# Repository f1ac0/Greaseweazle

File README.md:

# Greaseweazle
The Greaseweazle project by Keir Fraser is a USB floppy drive interface and software tool to read and write disk images to and from real floppies. It works at a low level so it can deal with formats that are unknown to the standard PC floppy disk controller.
https://github.com/keirf/Greaseweazle

The project in this repository is just a recreated "F1" board making use of the bare chips instead of a bluepill module, and designed to plug directly into a standard PC drive.
- It is small : it fits inside the 3.5" drive height and the ribbon width
- It is equipped with the female 34 pin connector to conveniently plug it in the drive, without a ribbon cable
- It connects to the PC with a micro USB cable
- It has a pass-through header for powering the drive (5v only). An external 5v/12v PSU is required only for drives requiring 12v or power hungry ones.
- It uses SMD stuff (maybe harder to solder)
- It is designed using the KiCAD EDA
- It works with the original "F1" Greaseweazle firmware and tool
- It is updated to support the DISKCHANGE signal and to be able to report as a "F1 plus" board. This is necessary for the WinUAE FloppyBridge plugin by Robert Smith (http://amiga.robsmithdev.co.uk/winuae) who added support to the Greaseweazle in addition to his original DrawBridge interface. Thank you !
- It does not have the "F7" features like double drive support

# Disclaimer
This is a hobbyist project, it comes with no warranty and no support.

This version is not endorsed by the original author, please don't bother him with issues you might have because of it.

I publish this work using the same license as the original : The Unlicense.

If you find it useful, please reward the original author.

# BOM
- 1x STM32F103C8T6 or CS32F103C8T6
- 1x 3.3v LDO, either SPX3819M5-L-3-3 or XC6206P332MR or equivalent
- 1x 8MHz HC-49 crystal
- 2x 1uF 0805 capacitors
- 3x 100nF 0805 capacitors
- 2x 22pf 0805 capacitors
- 2x 22 ohm 0805 resistors
- 1x 1K 0805 resistor
- 1x 10K 0805 resistor
- 1x 100K 0805 resistor (to reduce the BOM you can use a 10k)
- 1x 1K 0603x4 resistor array
- 1x optional 0805 LED and 0805 resistor (330 ohm or more)
- 1x Micro USB Female Socket B type
- 1x 2x17 2.54mm pin socket
- 1x FDD power cable

# Making it
Check for shorts at least between 5V, 3.3V, and GND traces before applying power !

The programming port does not need to be soldered since it needs to be programmed just once : you can just hold it in place during the few seconds required for programming.

For the software part, it works with the original "F1" firmware and tool.

There are ID pads on the bottom of the board :
- with ID pads left open, it will be identified as a "F1" version.
- recommended for FloppyBridge plugin : use a recent firmware and close ID0 on the "2" side, make sure the "1" side is open, then it will be identified as a "F1 plus".

To program the uC, I personally use a STLINK clone dongle with the stlink tool : https://github.com/stlink-org/stlink
```
st-flash --format ihex write Greaseweazle-F1-v0.??.hex
```
To update through the USB cable, bridge CK and GND on the programming port before connecting the USB cable, then enter
```
Greaseweazle/gw update
```

# Using it
Choose a PC drive. Do not use a Shugart drive from your Amiga. Prefer a 5v one that does not require a 12V rail.
- Plug the board to the 34 pin connector of the PC drive,
- If your drive is 5v only, plug the power cord from the Greaseweazle board to the power plug of the drive,
- If the drive needs 12v, or if your USB source does not deliver enough current, then use an external power supply instead,
- Plug a micro USB cable to the device,
- Then install it and use it like an original Greaseweazle device : https://github.com/keirf/Greaseweazle/wiki/Software-Installation
```
Greaseweazle/gw read mydisk.scp
Greaseweazle/gw write mydisk.scp
```

To use it with WinUAE, see : http://amiga.robsmithdev.co.uk/winuae

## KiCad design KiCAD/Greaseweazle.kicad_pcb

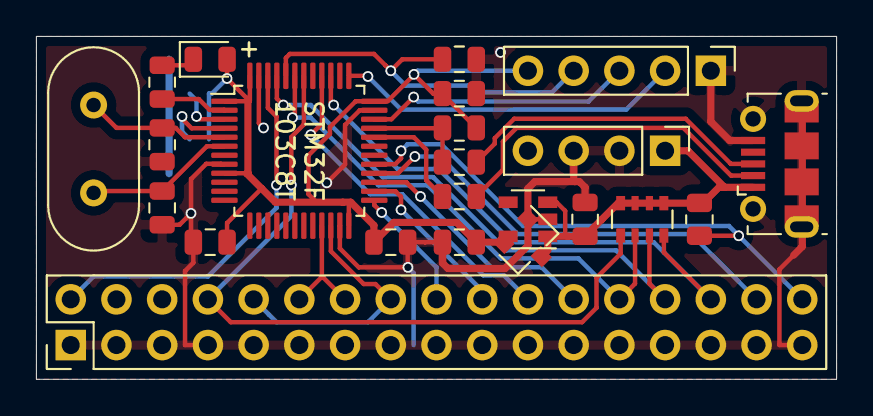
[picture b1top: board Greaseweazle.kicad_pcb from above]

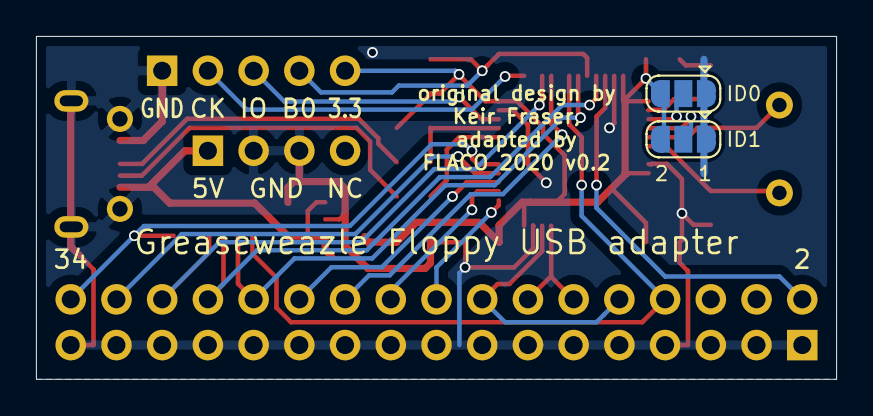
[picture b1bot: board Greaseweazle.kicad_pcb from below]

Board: 2 copper layers, 44.5 x 19.0 mm, 25 parts (2 on the bottom side), 29 nets.

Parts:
C1, C2: 22p; C_0805_2012Metric
C4, C5: 1u; C_0805_2012Metric
C6, C7, C8: 100n; C_0805_2012Metric
D1: Blue; LED_0805_2012Metric
J1: USB_B_Micro; USB_Micro-B_Molex-105017-0001
J2: PROG; PinHeader_1x05_P2.54mm_Vertical
J3: POWER; PinHeader_1x04_P2.54mm_Vertical
J4: Conn_02x17_Odd_Even; PinHeader_2x17_P2.54mm_Vertical
JP1: ID0; SolderJumper-3_P1.3mm_Open_RoundedPad1.0x1.5mm
JP2: ID1; SolderJumper-3_P1.3mm_Open_RoundedPad1.0x1.5mm
R2: 510; R_0805_2012Metric
R3: 100k; R_0805_2012Metric
R4: 1k; R_0805_2012Metric
R5: 10k; R_0805_2012Metric
R6, R7: 22; R_0805_2012Metric
RN1: 1k; R_Array_Convex_4x0603
U1: SPX3819M5-L-3-3; SOT-23-5
U2: STM32F103C8Tx; LQFP-48_7x7mm_P0.5mm
U3: XC6206PxxxMR; SOT-23
Y1: 8M; Crystal_HC49-U_Vertical

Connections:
+3V3: C5.1, C6.1, C7.1, C8.1, D1.2, J2.5, JP1.3, JP2.3, R5.1, U1.5, U2.1, U2.9, U2.24, U2.36, U2.48, U3.2
+5V: C4.1, J1.1, J3.1, R4.1, RN1.5, RN1.6, RN1.7, RN1.8, U1.1, U1.3, U3.3
/BOOT0: J2.4, R3.1, U2.44
/ID0: JP1.2, U2.3
/ID1: JP2.2, U2.4
/LED: R2.2, U2.2
/SWCLK: J2.2, U2.37
/SWDIO: J2.3, U2.34
/USB_D+: J1.3, R7.1
/USB_D-: J1.2, R6.1
/_DENSEL: J4.2, U2.46
/_DIR: J4.18, U2.25
/_DKRD: J4.30, RN1.4, U2.39
/_DKWD: J4.22, U2.40
/_DKWE: J4.24, U2.27
/_DSKCHG: J4.34, R4.2, U2.29
/_INDEX: J4.8, RN1.1, U2.42
/_MTR: J4.10, J4.16, U2.22
/_SEL: J4.12, J4.14, U2.21
/_SIDE: J4.32, U2.28
/_STEP: J4.20, U2.26
/_TRK0: J4.26, RN1.2, U2.43
/_WRPROT: J4.28, RN1.3, U2.45
GND: C1.2, C2.2, C4.2, C5.2, C6.2, C7.2, C8.2, J1.5, J1.6, J2.1, J3.2, J3.3, J4.1, J4.3, J4.5, J4.7, J4.9, J4.11, J4.13, J4.15, J4.17, J4.19, J4.21, J4.23, J4.25, J4.27, J4.29, J4.31, J4.33, JP1.1, JP2.1, R3.2, U1.2, U2.8, U2.23, U2.35, U2.47, U3.1
unnamed: C1.1, U2.5, Y1.1
unnamed: C2.1, U2.6, Y1.2
unnamed: D1.1, R2.1
unnamed: R5.2, R7.2, U2.33
unnamed: R6.2, U2.32

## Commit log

2020-07-31 Respository init with v0.1 KiCAD files, Readme and License
2021-06-08 Kicad : 0.2 with additional regulator footprint, DISKCHANGE signal and ID jumpers
2022-02-16 Photo, InteractiveHtmlBom and README

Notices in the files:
KiCAD/Greaseweazle.kicad_pcb:
FLACO 2019, original schematic by Keir Fraser under The Unlicense
